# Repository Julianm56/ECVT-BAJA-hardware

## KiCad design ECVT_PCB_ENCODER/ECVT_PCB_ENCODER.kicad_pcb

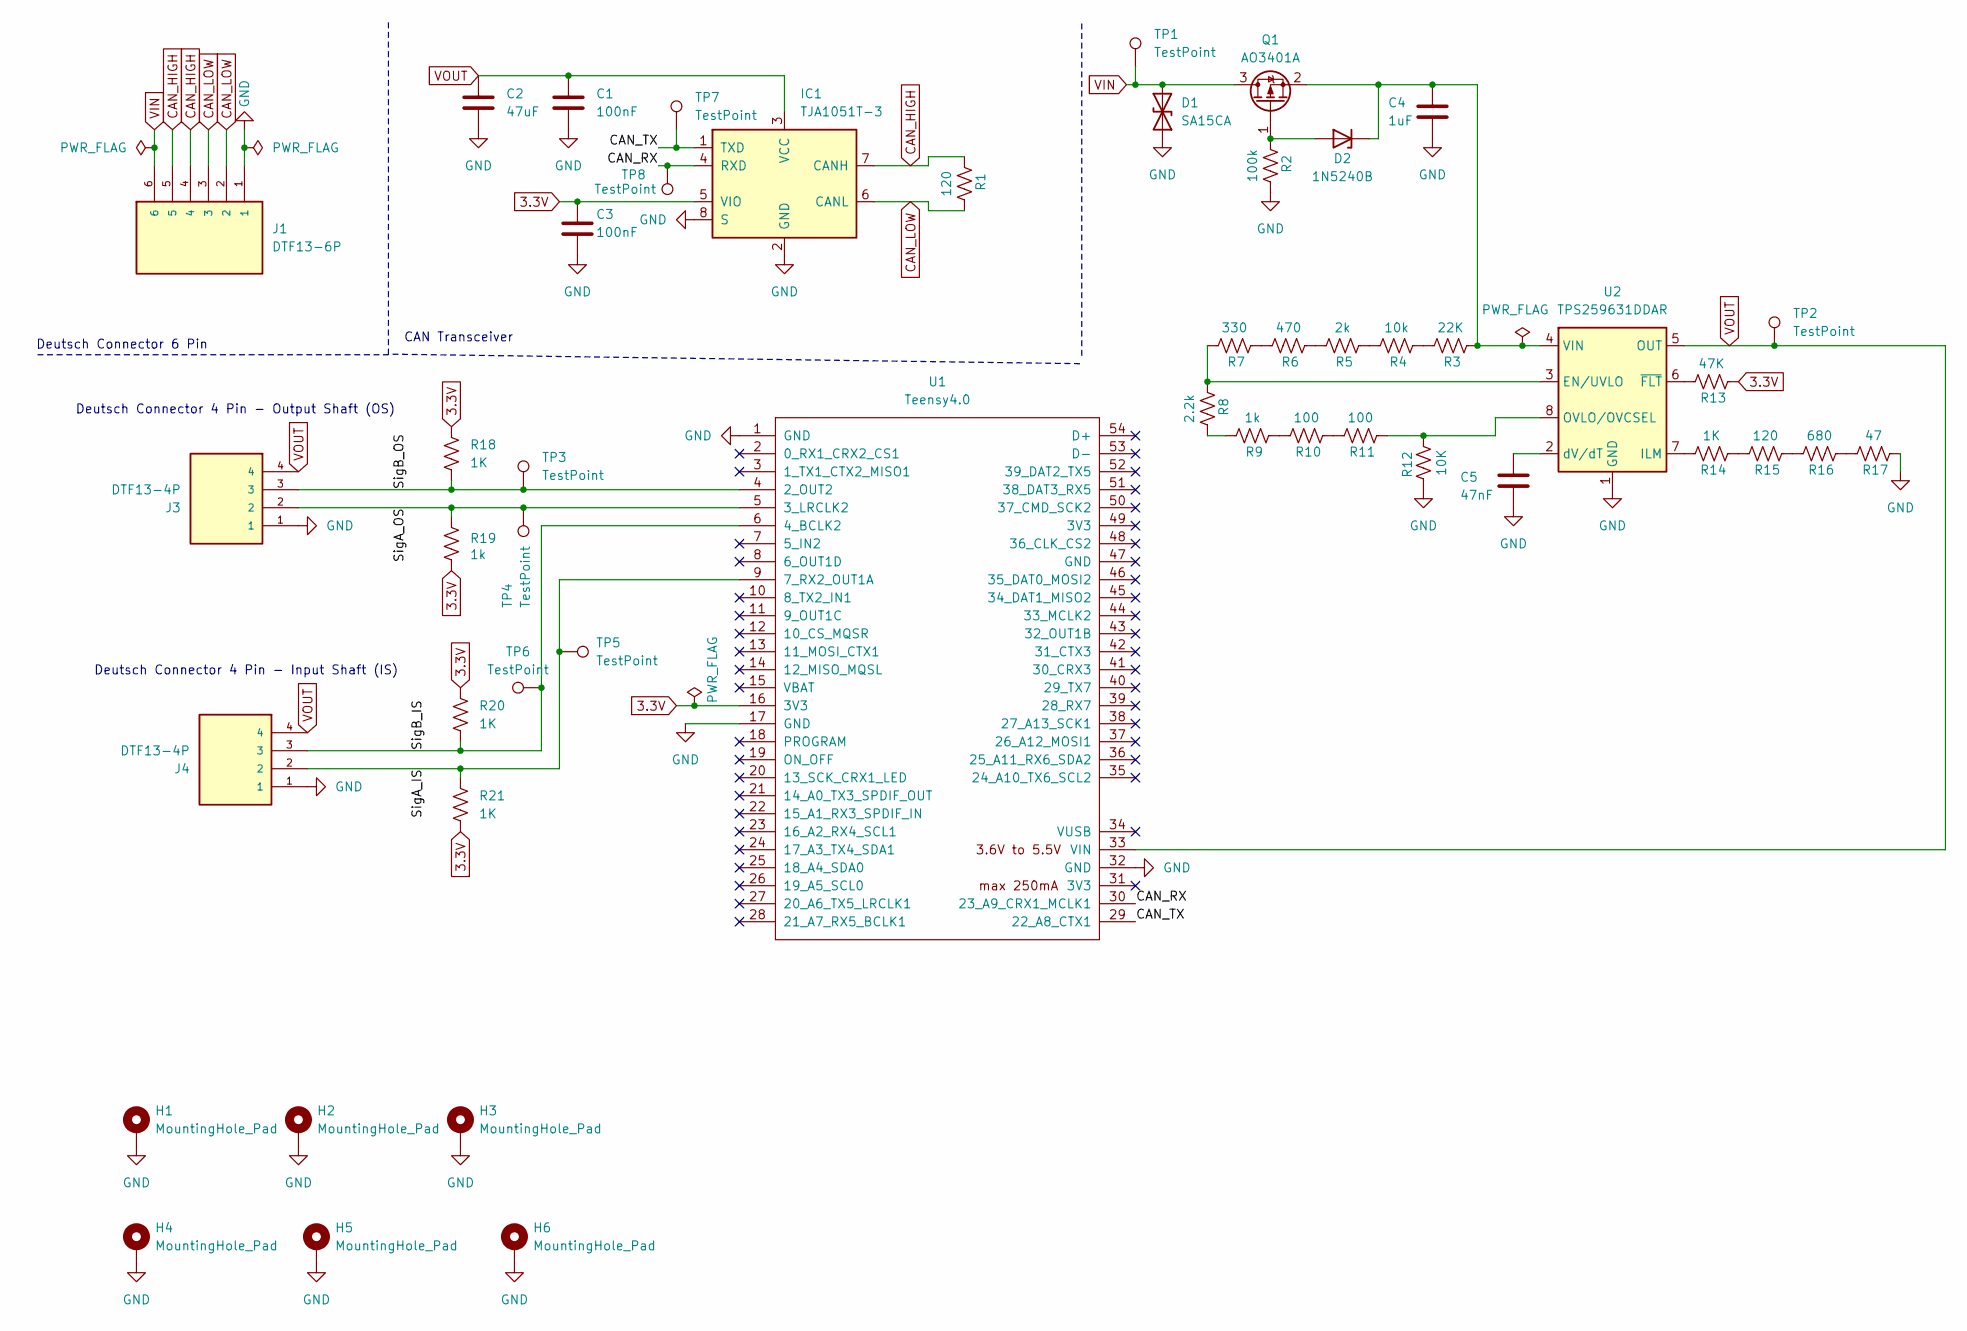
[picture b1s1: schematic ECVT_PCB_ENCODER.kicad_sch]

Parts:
C1, C3: 100nF; C_Disc_D5.0mm_W2.5mm_P5.00mm
C2: 47uF; C_Disc_D5.0mm_W2.5mm_P5.00mm
C4: 1uF; C_Disc_D5.0mm_W2.5mm_P5.00mm
C5: 47nF; C_Disc_D5.0mm_W2.5mm_P5.00mm
D1: SA15CA; D_DO-41_SOD81_P10.16mm_Horizontal
D2: 1N5240B; D_DO-41_SOD81_P10.16mm_Horizontal
H1, H2, H3, H4, H5, H6: MountingHole_Pad; MountingHole_3.2mm_M3_DIN965_Pad
IC1: TJA1051T-3; SOIC-8_3.9x4.9mm_P1.27mm
J1: DTF13-6P; TE_DTF13-6P
J3, J4: DTF13-4P; TE_DTF13-4P; PARTREV NC
Q1: AO3401A; SOT-23
R1, R15: 120; R_Axial_DIN0207_L6.3mm_D2.5mm_P10.16mm_Horizontal
R2: 100k; R_Axial_DIN0207_L6.3mm_D2.5mm_P10.16mm_Horizontal
R3: 22K; R_Axial_DIN0207_L6.3mm_D2.5mm_P10.16mm_Horizontal
R4: 10k; R_Axial_DIN0207_L6.3mm_D2.5mm_P10.16mm_Horizontal
R5: 2k; R_Axial_DIN0207_L6.3mm_D2.5mm_P10.16mm_Horizontal
R6: 470; R_Axial_DIN0207_L6.3mm_D2.5mm_P10.16mm_Horizontal
R7: 330; R_Axial_DIN0207_L6.3mm_D2.5mm_P10.16mm_Horizontal
R8: 2.2k; R_Axial_DIN0207_L6.3mm_D2.5mm_P10.16mm_Horizontal
R9, R19: 1k; R_Axial_DIN0207_L6.3mm_D2.5mm_P10.16mm_Horizontal
R10, R11: 100; R_Axial_DIN0207_L6.3mm_D2.5mm_P10.16mm_Horizontal
R12: 10K; R_Axial_DIN0207_L6.3mm_D2.5mm_P10.16mm_Horizontal
R13: 47K; R_Axial_DIN0207_L6.3mm_D2.5mm_P10.16mm_Horizontal
R14, R18, R20, R21: 1K; R_Axial_DIN0207_L6.3mm_D2.5mm_P10.16mm_Horizontal
R16: 680; R_Axial_DIN0207_L6.3mm_D2.5mm_P10.16mm_Horizontal
R17: 47; R_Axial_DIN0207_L6.3mm_D2.5mm_P10.16mm_Horizontal
TP1, TP2, TP3, TP4, TP5, TP6, TP7, TP8: TestPoint; TestPoint_Pad_D1.5mm
U1: Teensy4.0; Teensy40
U2: TPS259631DDAR; TI_SO-PowerPAD-8_ThermalVias

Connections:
3.3V: C3.1, IC1.5 (VIO), R13.1, R18.1, R19.2, R20.1, R21.2, U1.16 (3V3)
/CAN_RX: IC1.4 (RXD), TP8.1 (1_1), U1.30 (23_A9_CRX1_MCLK1)
/CAN_TX: IC1.1 (TXD), TP7.1 (1_1), U1.29 (22_A8_CTX1)
/SigA_IS: J4.2, R21.1, TP5.1 (1_1), U1.9 (7_RX2_OUT1A)
/SigA_OS: J3.2, R19.1, TP4.1 (1_1), U1.5 (3_LRCLK2)
/SigB_IS: J4.3, R20.2, TP6.1 (1_1), U1.6 (4_BCLK2)
/SigB_OS: J3.3, R18.2, TP3.1 (1_1), U1.4 (2_OUT2)
CAN_HIGH: IC1.7 (CANH), J1.4, J1.5, R1.1
CAN_LOW: IC1.6 (CANL), J1.2, J1.3, R1.2
GND: C1.2, C2.2, C3.2, C4.2, C5.2, D1.2 (A2), H1.1 (1_1), H2.1 (1_1), H3.1 (1_1), H4.1 (1_1), H5.1 (1_1), H6.1 (1_1), IC1.2 (GND), IC1.8 (S), J1.1, J3.1, J4.1, R2.2, R12.1, R17.1, U1.1 (GND), U1.17 (GND), U1.32 (GND), U2.1 (GND), U2.9 (GND)
unnamed: D2.2 (A), Q1.1 (G), R2.1
unnamed: C4.1, D2.1 (K), Q1.2 (S), R3.1, U2.4 (VIN)
unnamed: R3.2, R4.1
unnamed: R4.2, R5.1
unnamed: R5.2, R6.1
unnamed: R6.2, R7.1
unnamed: R8.2, R9.2
unnamed: R10.1, R11.2
unnamed: R9.1, R10.2
unnamed: R14.1, R15.2
unnamed: R15.1, R16.2
unnamed: R16.1, R17.2
unnamed: R7.2, R8.1, U2.3 (EN/UVLO)
unnamed: R14.2, U2.7 (ILM)
unnamed: R11.1, R12.2, U2.8 (OVLO/OVCSEL)
unnamed: C5.1, U2.2 (dV/dT)
unnamed: R13.2, U2.6 (~FLT)
VIN: D1.1 (A1), J1.6, Q1.3 (D), TP1.1 (1_1)
VOUT: C1.1, C2.1, IC1.3 (VCC), J3.4, J4.4, TP2.1 (1_1), U1.33 (VIN), U2.5 (OUT)

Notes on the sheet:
CAN Transceiver
Deutsch Connector 6 Pin
Deutsch Connector 4 Pin - Output Shaft (OS)
Deutsch Connector 4 Pin - Input Shaft (IS)

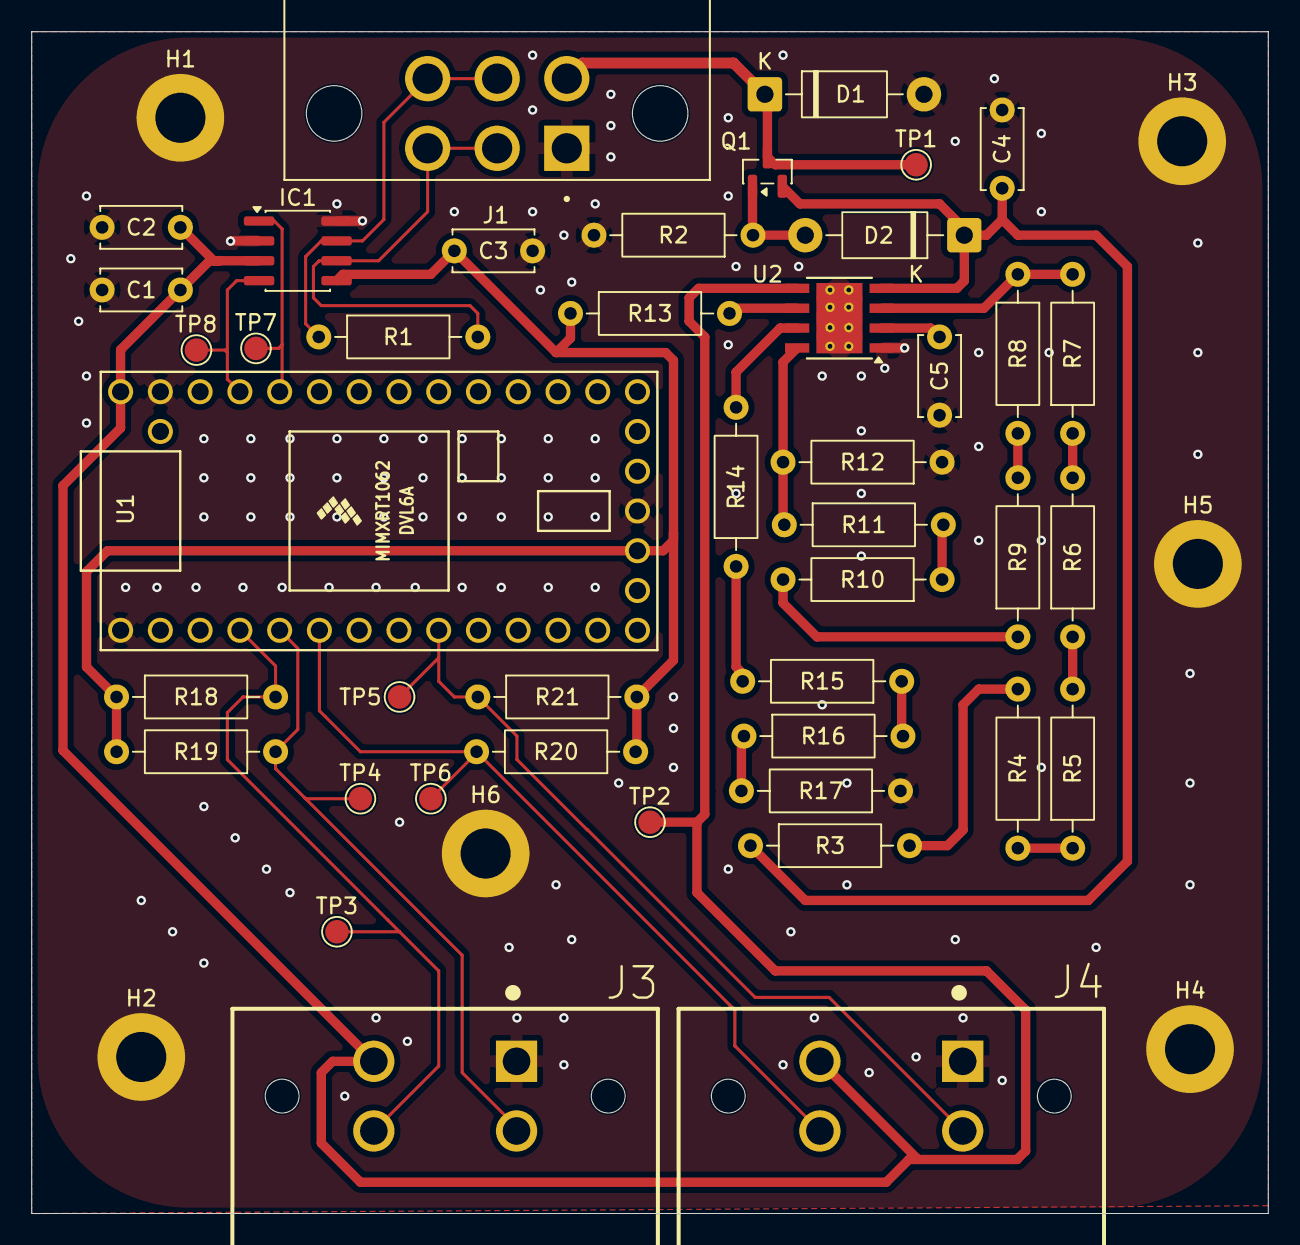
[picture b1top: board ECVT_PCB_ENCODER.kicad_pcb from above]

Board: 2 copper layers, 79.0 x 75.5 mm, 49 parts (0 on the bottom side), 29 nets.

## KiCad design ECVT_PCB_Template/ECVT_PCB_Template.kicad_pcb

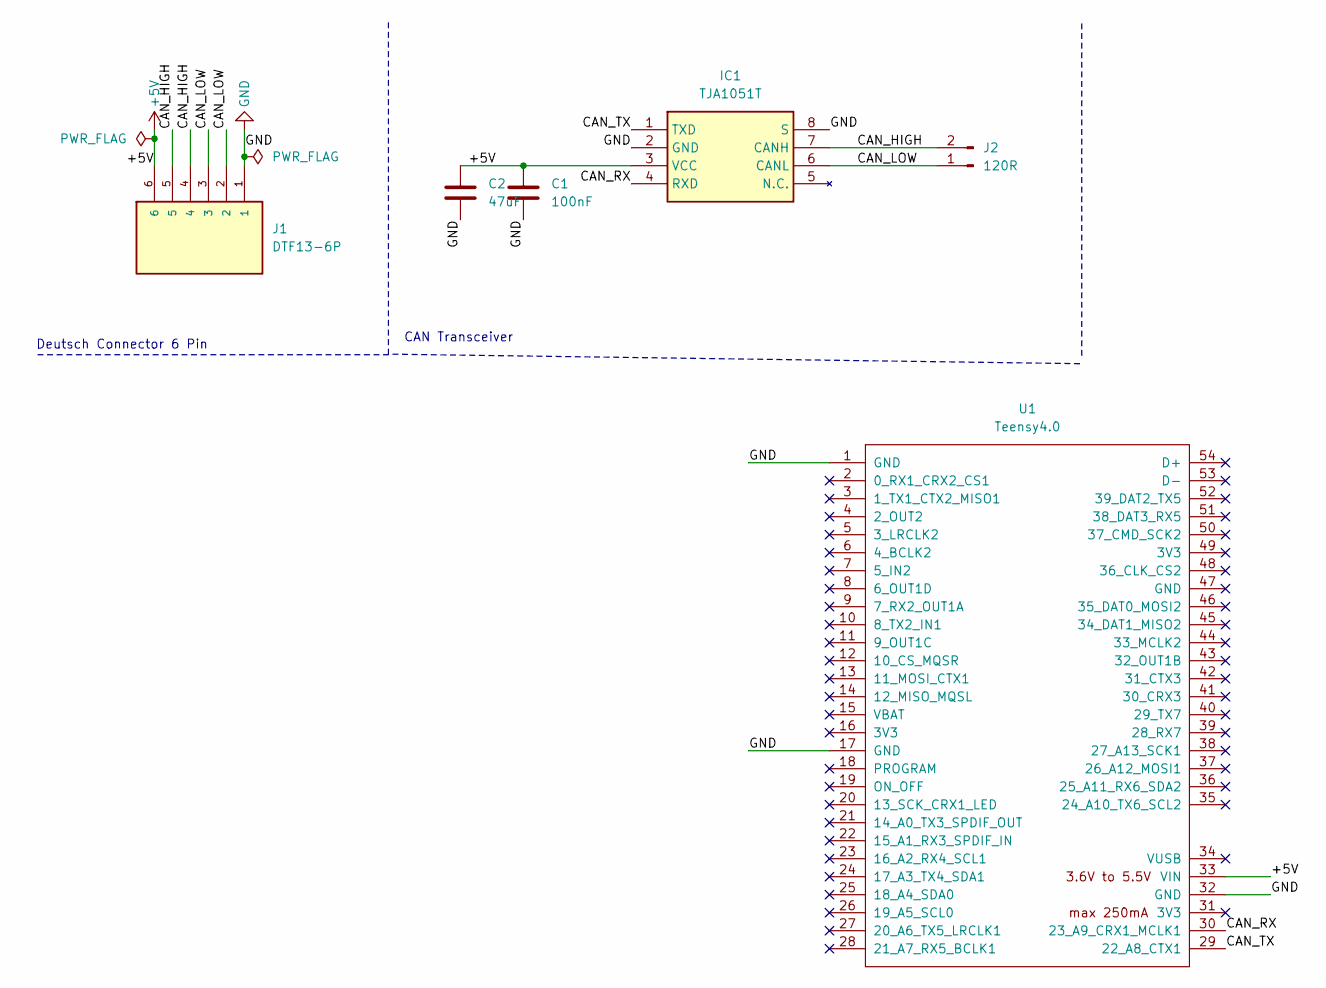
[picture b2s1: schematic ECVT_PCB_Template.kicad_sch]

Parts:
C1: 100nF; C_1206_3216Metric_Pad1.33x1.80mm_HandSolder
C2: 47uF; C_1206_3216Metric_Pad1.33x1.80mm_HandSolder
IC1: TJA1051T; SOIC127P600X175-8N; Manufacturer_Part_Number TJA1051T; Mouser Part Number N/A
J1: DTF13-6P; TE_DTF13-6P
J2: 120R; PinHeader_1x02_P1.00mm_Vertical
U1: Teensy4.0; Teensy40

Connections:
+5V: C1.1, C2.1, IC1.3 (VCC), J1.6, U1.33 (VIN)
/CAN_HIGH: IC1.7 (CANH), J1.4, J1.5, J2.2
/CAN_LOW: IC1.6 (CANL), J1.2, J1.3, J2.1
/CAN_RX: IC1.4 (RXD), U1.30 (23_A9_CRX1_MCLK1)
/CAN_TX: IC1.1 (TXD), U1.29 (22_A8_CTX1)
GND: C1.2, C2.2, IC1.2 (GND), IC1.8 (S), J1.1, U1.1 (GND), U1.17 (GND), U1.32 (GND)

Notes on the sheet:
CAN Transceiver
Deutsch Connector 6 Pin

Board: 2 copper layers, 6 parts (0 on the bottom side), 6 nets, no tracks yet.
